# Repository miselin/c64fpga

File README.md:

# FPGA Boards for Commodore 64

These boards connect to the User and Expansion ports of the Commmodore 64 and
break the pins out onto the I/O in the [Mercury FPGA](https://www.micro-nova.com/mercury)
development board.

This is pin-compatible with either the Mercury or the Mercury 2, the latter
using a more modern Artix-7 FPGA than the Mercury's Spartan 3A.

## Cartridge Board

This board requires two 4-channel I2C-safe bidirectional logic level shifters
as the cartridge pinout has 44 pins, but the Mercury board only has 30 5V-tolerant
GPIO pins. The level shifter ensures the 5V TTL signals from the Commodore 64
are shifted down to 3.3V for the FPGA direct I/O pins.

These can be [found on Adafruit](https://www.adafruit.com/product/757).

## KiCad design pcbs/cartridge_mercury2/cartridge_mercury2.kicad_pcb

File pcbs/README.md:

# PCB Designs

This directory contains KiCad projects for the PCB designs
associated with the project.

`cartridge_mercury1` contains the PCB schematic to support the original
[Mercury FPGA board](https://www.micro-nova.com/mercury). This version
of the Mercury only has 30 5V-tolerant GPIOs, which means level shifters
are necessary to bring the Commodore 64's 5V TTL down to 3.3V to interface
with the FPGA I/O pins.

The [Mercury 2 FPGA board](https://www.micro-nova.com/mercury-2) on the
other hand supports 40 5V-tolerant GPIOs, which makes the PCB simpler and
does not require extra level shifting. A design to take advantage of this
is in the `cartridge_mercury2` directory.

There is no current design in progress that integrates the FPGA directly
without utilizing an additional product.

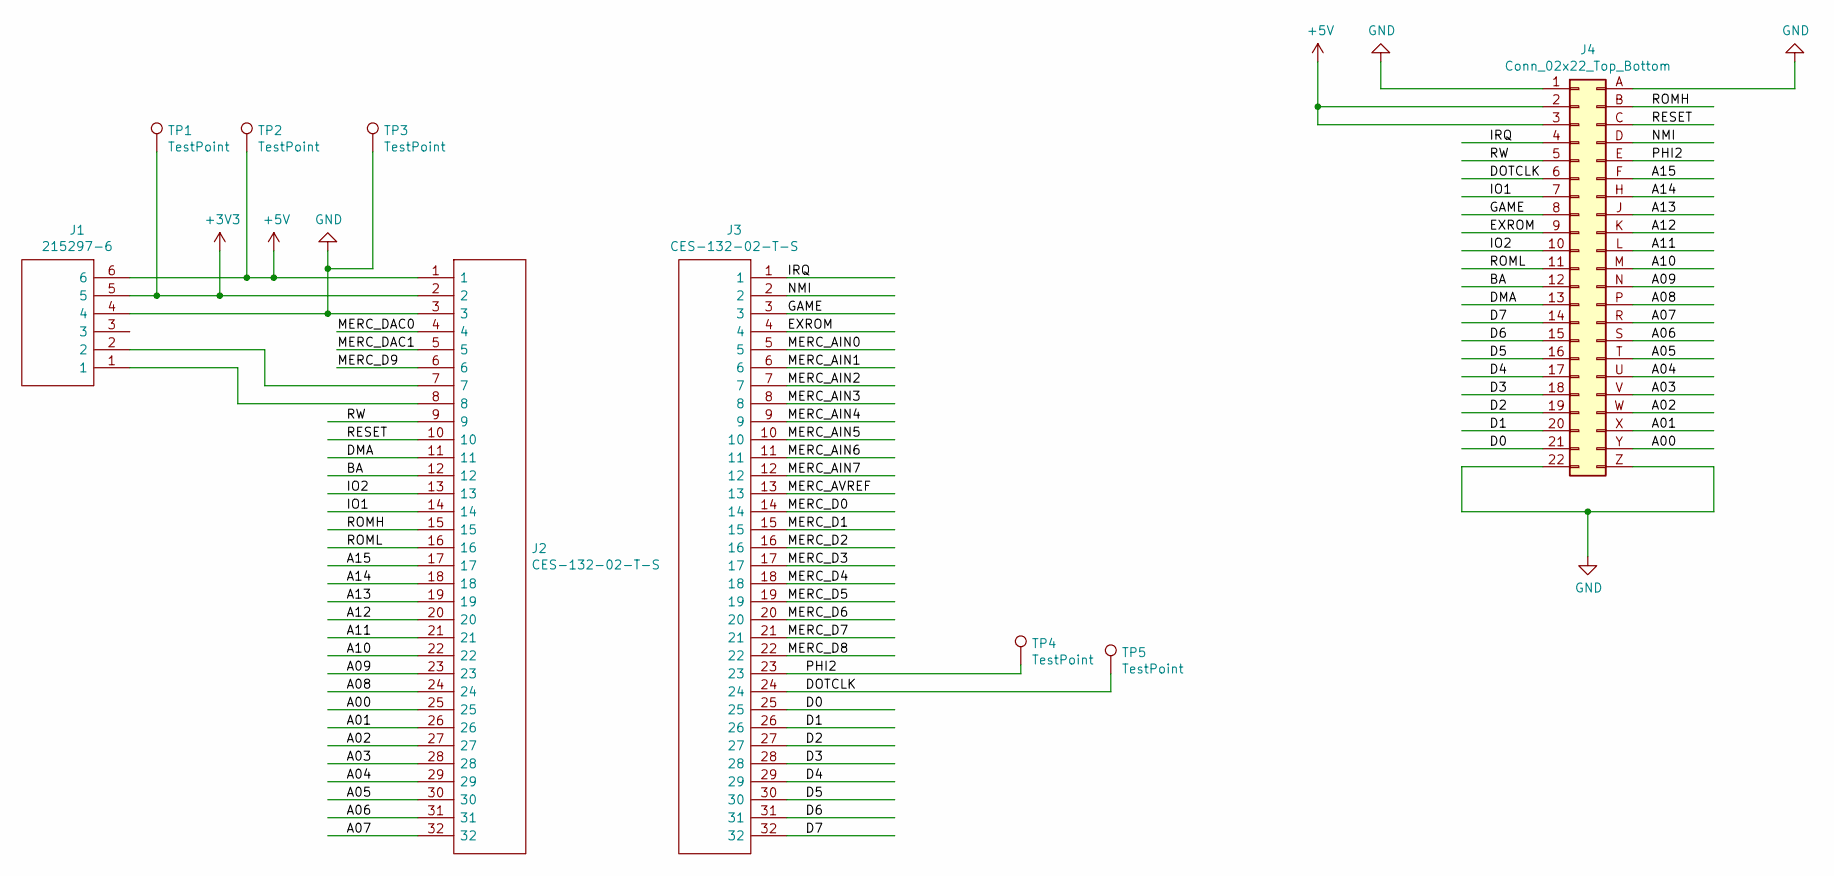
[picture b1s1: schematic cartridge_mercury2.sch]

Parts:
J1: 215297-6; 2152976; Mouser Part Number 571-215297-6
J2, J3: CES-132-02-T-S; CES-132-XX-Y-S; Manufacturer_Part_Number CES-132-02-T-S
J4: Conn_02x22_Top_Bottom; C64-Cart
TP1, TP2, TP3, TP4, TP5: TestPoint; TestPoint_THTPad_D1.5mm_Drill0.7mm

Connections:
+3V3: J1.5, J2.2, TP1.1
+5V: J1.6, J2.1, J4.2, J4.3, TP2.1
/A00: J2.25, J4.Y (Pin_43)
/A01: J2.26, J4.X (Pin_42)
/A02: J2.27, J4.W (Pin_41)
/A03: J2.28, J4.V (Pin_40)
/A04: J2.29, J4.U (Pin_39)
/A05: J2.30, J4.T (Pin_38)
/A06: J2.31, J4.S (Pin_37)
/A07: J2.32, J4.R (Pin_36)
/A08: J2.24, J4.P (Pin_35)
/A09: J2.23, J4.N (Pin_34)
/A10: J2.22, J4.M (Pin_33)
/A11: J2.21, J4.L (Pin_32)
/A12: J2.20, J4.K (Pin_31)
/A13: J2.19, J4.J (Pin_30)
/A14: J2.18, J4.H (Pin_29)
/A15: J2.17, J4.F (Pin_28)
/BA: J2.12, J4.12
/D0: J3.25, J4.21
/D1: J3.26, J4.20
/D2: J3.27, J4.19
/D3: J3.28, J4.18
/D4: J3.29, J4.17
/D5: J3.30, J4.16
/D6: J3.31, J4.15
/D7: J3.32, J4.14
/DMA: J2.11, J4.13
/DOTCLK: J3.24, J4.6, TP5.1
/EXROM: J3.4, J4.9
/GAME: J3.3, J4.8
/IO1: J2.14, J4.7
/IO2: J2.13, J4.10
/IRQ: J3.1, J4.4
/MERC_AIN0: J3.5
/MERC_AIN1: J3.6
/MERC_AIN2: J3.7
/MERC_AIN3: J3.8
/MERC_AIN4: J3.9
/MERC_AIN5: J3.10
/MERC_AIN6: J3.11
/MERC_AIN7: J3.12
/MERC_AVREF: J3.13
/MERC_D0: J3.14
/MERC_D1: J3.15
/MERC_D2: J3.16
/MERC_D3: J3.17
/MERC_D4: J3.18
/MERC_D5: J3.19
/MERC_D6: J3.20
/MERC_D7: J3.21
/MERC_D8: J3.22
/MERC_D9: J2.6
/MERC_DAC0: J2.4
/MERC_DAC1: J2.5
/NMI: J3.2, J4.D (Pin_26)
/PHI2: J3.23, J4.E (Pin_27), TP4.1
/RESET: J2.10, J4.C (Pin_25)
/ROMH: J2.15, J4.B (Pin_24)
/ROML: J2.16, J4.11
/RW: J2.9, J4.5
GND: J1.4, J2.3, J4.1, J4.22, J4.A (Pin_23), J4.Z (Pin_44), TP3.1
unnamed: J1.1, J2.8
unnamed: J1.2, J2.7

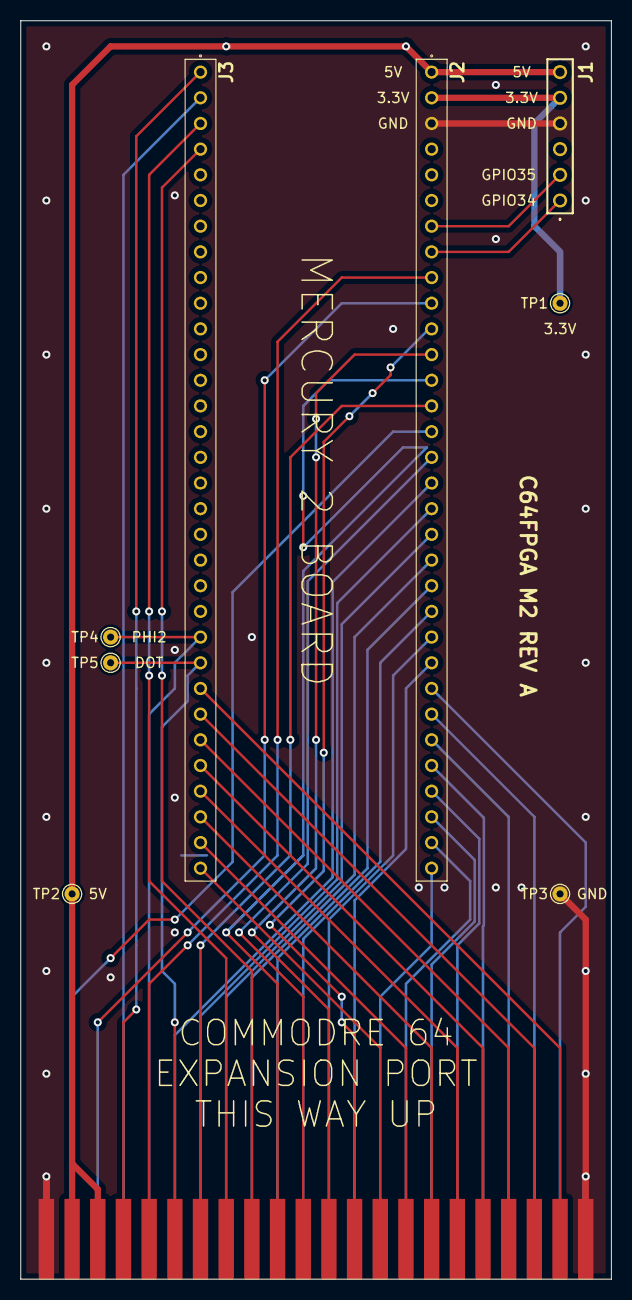
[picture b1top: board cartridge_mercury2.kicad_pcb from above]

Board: 2 copper layers, 58.4 x 124.5 mm, 9 parts (0 on the bottom side), 43 nets.

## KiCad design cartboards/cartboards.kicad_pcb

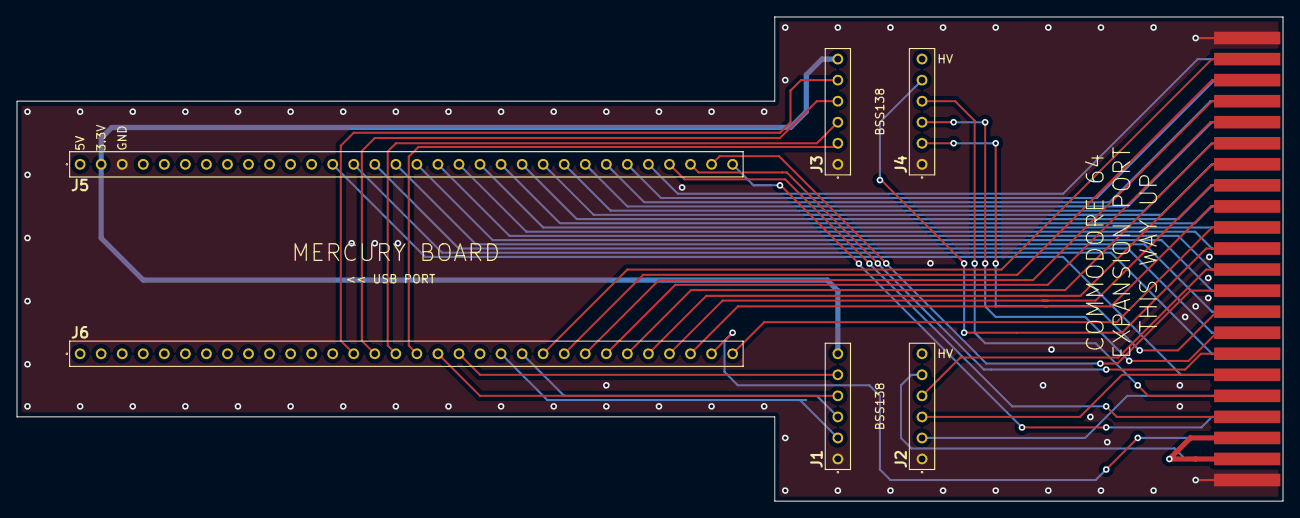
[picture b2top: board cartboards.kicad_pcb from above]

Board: 4 copper layers, 152.8 x 58.4 mm, 7 parts (0 on the bottom side), 49 nets.

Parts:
C64: Conn_02x22_Counter_Clockwise; C64-Cart
J1, J2, J3, J4: CES-106-01-T-S; CES-106-XX-Y-S
J5, J6: CES-132-02-T-S; CES-132-XX-Y-S

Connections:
+3V3: J1.6, J3.6, J5.2
/CLK0: J1.2, J6.21
/CLK1: J1.3, J6.22
/DATA0: C64.21, J6.23
/DATA1: C64.20, J6.24
/DATA2: C64.19, J6.25
/DATA3: C64.18, J6.26
/DATA4: C64.17, J6.27
/DATA5: C64.16, J6.28
/DATA6: C64.15, J6.29
/DATA7: C64.14, J6.30
/DIO0: J3.5, J6.14
/DIO1: J3.4, J6.15
/DIO2: J3.3, J6.16
/DIO3: J3.2, J6.17
/DIO4: J1.4, J6.18
/DIO5: J1.5, J6.19
C64_1_GND: C64.1, C64.22, C64.A, C64.Z, J1.1, J2.1, J3.1, J4.1, J5.3
C64_2_5V: C64.2, C64.3, J2.6, J4.6, J5.1
C64_4_IRQ: C64.4, J5.29
C64_5_RW: C64.5, J4.4
C64_6_DOTCLK: C64.6, J2.3
C64_7_IO1: C64.7, J5.30
C64_8_GAME: C64.8, J4.3
C64_9_EXROM: C64.9, J4.2
C64_10_IO2: C64.10, J5.31
C64_11_ROML: C64.11, J2.4
C64_12_BA: C64.12, J4.5
C64_13_DMA: C64.13, J6.32
C64_B_ROMH: C64.B, J2.5
C64_C_RESET: C64.C, J6.31
C64_D_NMI: C64.D, J5.32
C64_E_PHI2: C64.E, J2.2
C64_F_A15: C64.F, J5.13
C64_H_A14: C64.H, J5.14
C64_J_A13: C64.J, J5.15
C64_K_A12: C64.K, J5.16
C64_L_A11: C64.L, J5.17
C64_M_A10: C64.M, J5.18
C64_N_A9: C64.N, J5.19
C64_P_A8: C64.P, J5.20
C64_R_A7: C64.R, J5.21
C64_S_A6: C64.S, J5.22
C64_T_A5: C64.T, J5.23
C64_U_A4: C64.U, J5.24
C64_V_A3: C64.V, J5.25
C64_W_A2: C64.W, J5.26
C64_X_A1: C64.X, J5.27
C64_Y_A0: C64.Y, J5.28

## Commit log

2021-11-23 Fix VHDL, bitstream can be generated now.
2021-11-27 Tweak trace width for power in schematics
2021-11-27 Rename PCB design directory to prep for second design
2021-11-27 Add FPGA daughterboard for Mercury-2 board
